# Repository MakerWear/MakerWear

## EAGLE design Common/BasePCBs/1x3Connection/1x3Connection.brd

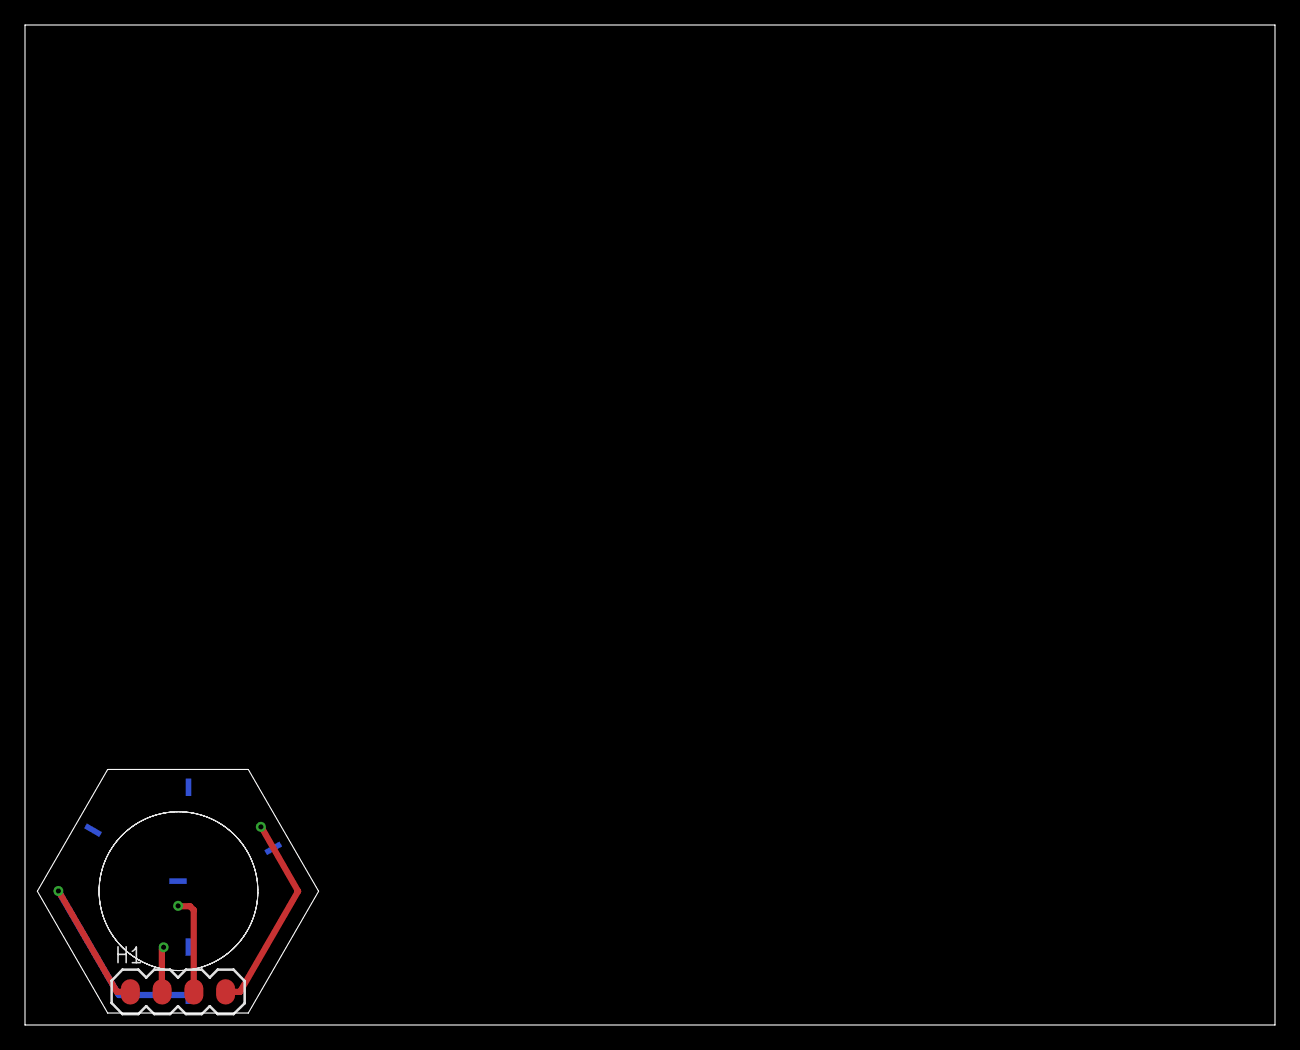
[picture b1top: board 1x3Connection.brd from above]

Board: 2 copper layers, 100.0 x 80.0 mm, 7 parts (0 on the bottom side), 4 nets.

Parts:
CON1, CON2, CON3, CON4, CON5, CON6: SHIELD_FINGER0820; SHIELD_FINGER_PKG
H1: 1X04_NO_HOLES

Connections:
GND: CON4.P1, CON4.P2, H1.3
PWR: CON5.P1, CON5.P2, H1.2
SIN: CON6.P1, CON6.P2, H1.1
SOUT: CON1.P1, CON1.P2, CON2.P1, CON2.P2, CON3.P1, CON3.P2, H1.4

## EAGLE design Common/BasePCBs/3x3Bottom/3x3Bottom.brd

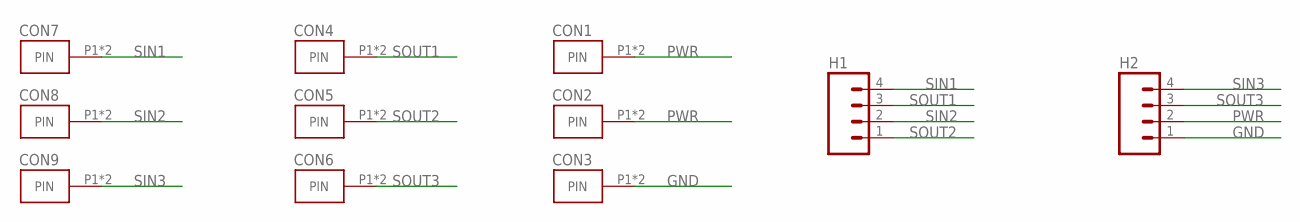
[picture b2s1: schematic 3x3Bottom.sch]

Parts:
CON1, CON2, CON3, CON4, CON5, CON6, CON7, CON8, CON9: SHIELD_FINGER0820; SHIELD_FINGER_PKG
H1, H2: M04; 1X04_NO_HOLES

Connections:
GND: CON3.P1, CON3.P2, H2.1
PWR: CON1.P1, CON1.P2, CON2.P1, CON2.P2, H2.2
SIN1: CON7.P1, CON7.P2, H1.4
SIN2: CON8.P1, CON8.P2, H1.2
SIN3: CON9.P1, CON9.P2, H2.4
SOUT1: CON4.P1, CON4.P2, H1.3
SOUT2: CON5.P1, CON5.P2, H1.1
SOUT3: CON6.P1, CON6.P2, H2.3

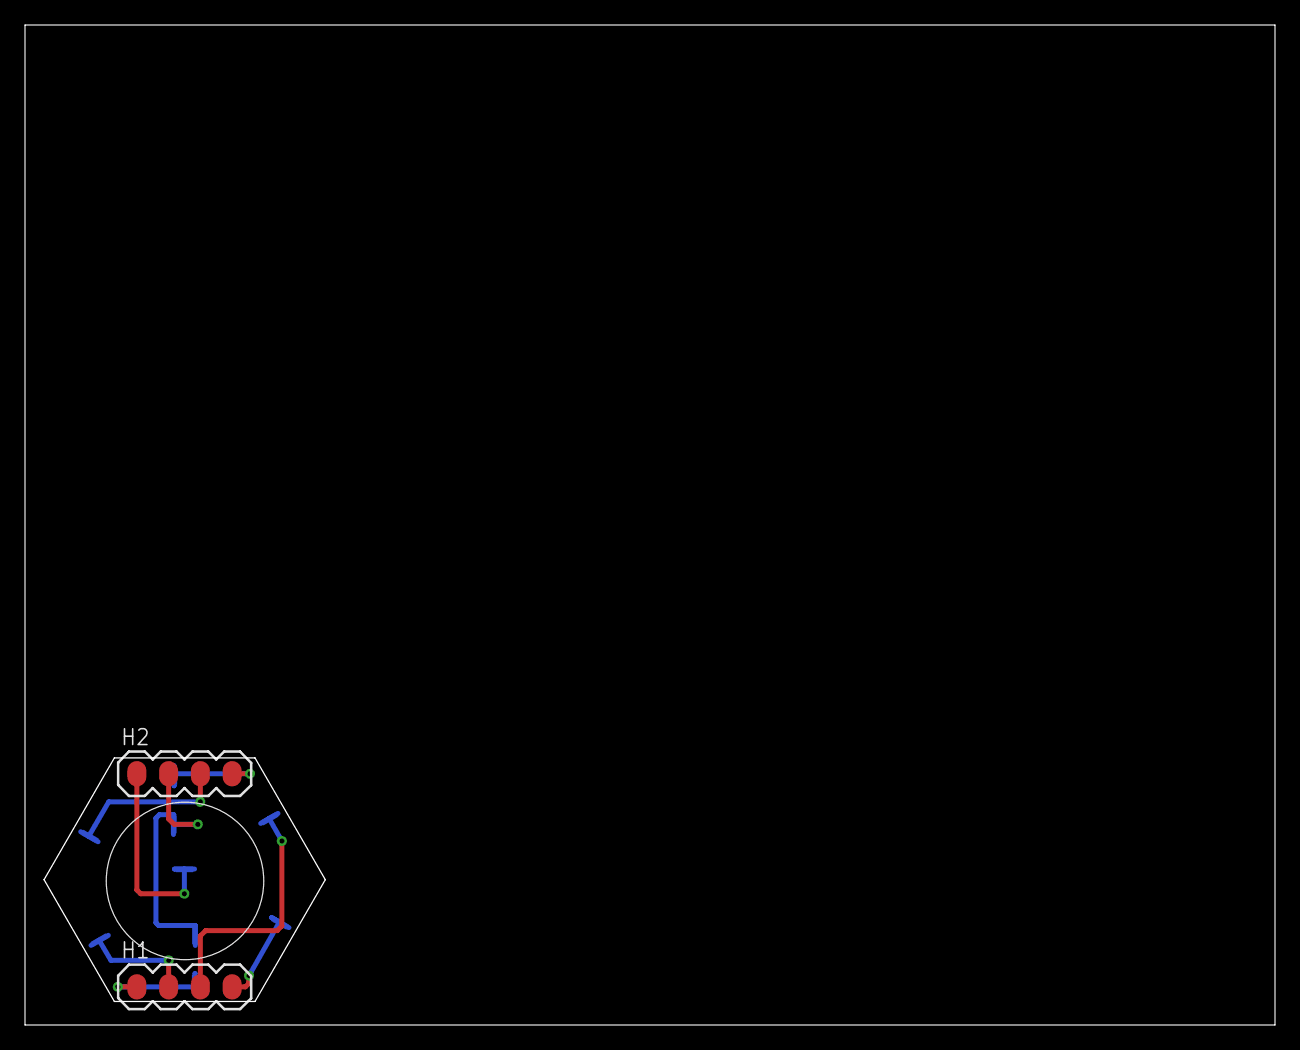
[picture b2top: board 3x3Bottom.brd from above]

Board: 2 copper layers, 100.0 x 80.0 mm, 11 parts (0 on the bottom side), 8 nets.

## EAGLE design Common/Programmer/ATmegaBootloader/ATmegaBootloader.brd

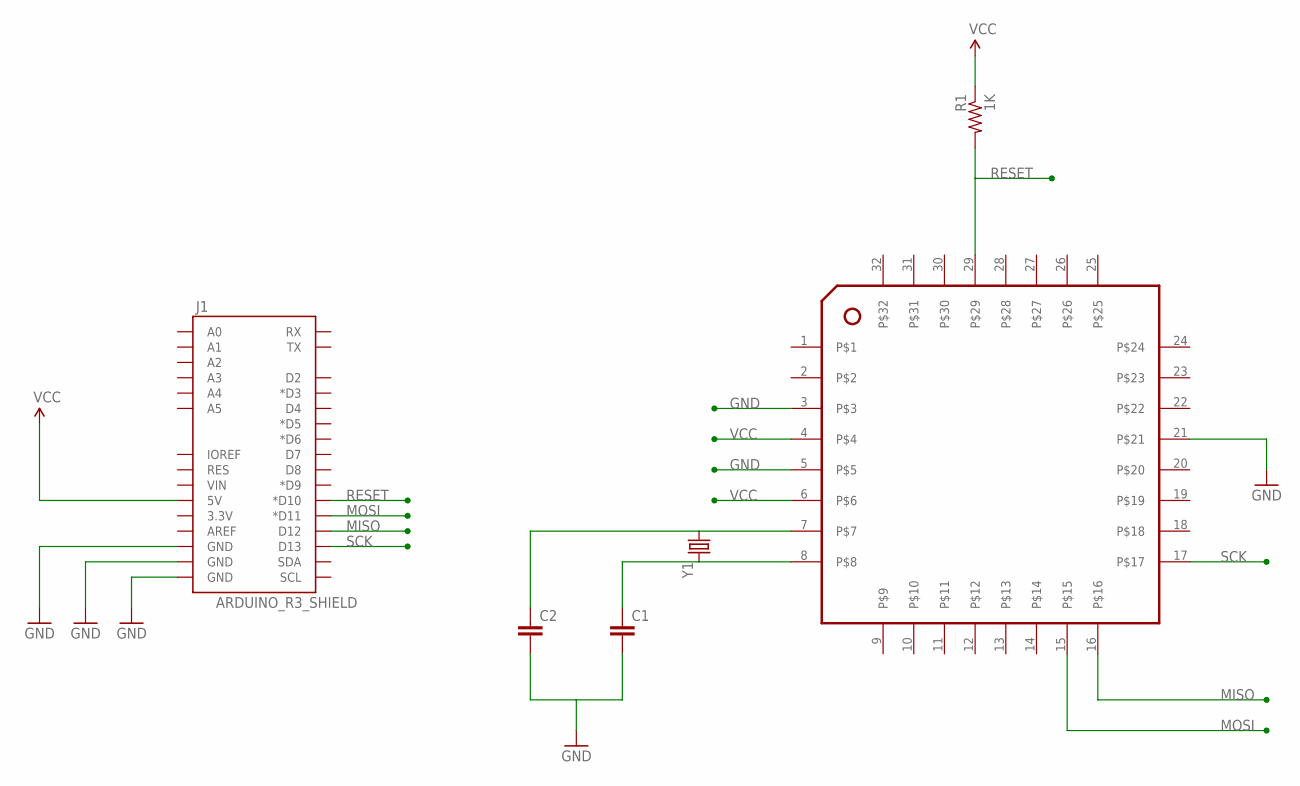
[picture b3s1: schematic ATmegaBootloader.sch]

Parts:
C1, C2: 0.1UF-50V-20%(PTH)KIT-EZ; CAP-PTH-SMALL-KIT
J1: ARDUINO_R3_SHIELD; UNO_R3_SHIELD
R1: 1K; AXIAL-0.3
U$1: ATMEGA-TQFP-BREAKOUT; TQFP32-BREAKOUT
Y1: CRYSTALHC49US; HC49US

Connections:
GND: C1.2, C2.2, J1.GND@0 (GND), J1.GND@1 (GND), J1.GND@2 (GND), U$1.3, U$1.5, U$1.21
MISO: J1.D12, U$1.16
MOSI: J1.D11 (*D11), U$1.15
unnamed: C2.1, U$1.7, Y1.1
unnamed: C1.1, U$1.8, Y1.2
RESET: J1.D10 (*D10), R1.P$2 (2), U$1.29
SCK: J1.D13, U$1.17
VCC: J1.5V, R1.P$1 (1), U$1.4, U$1.6

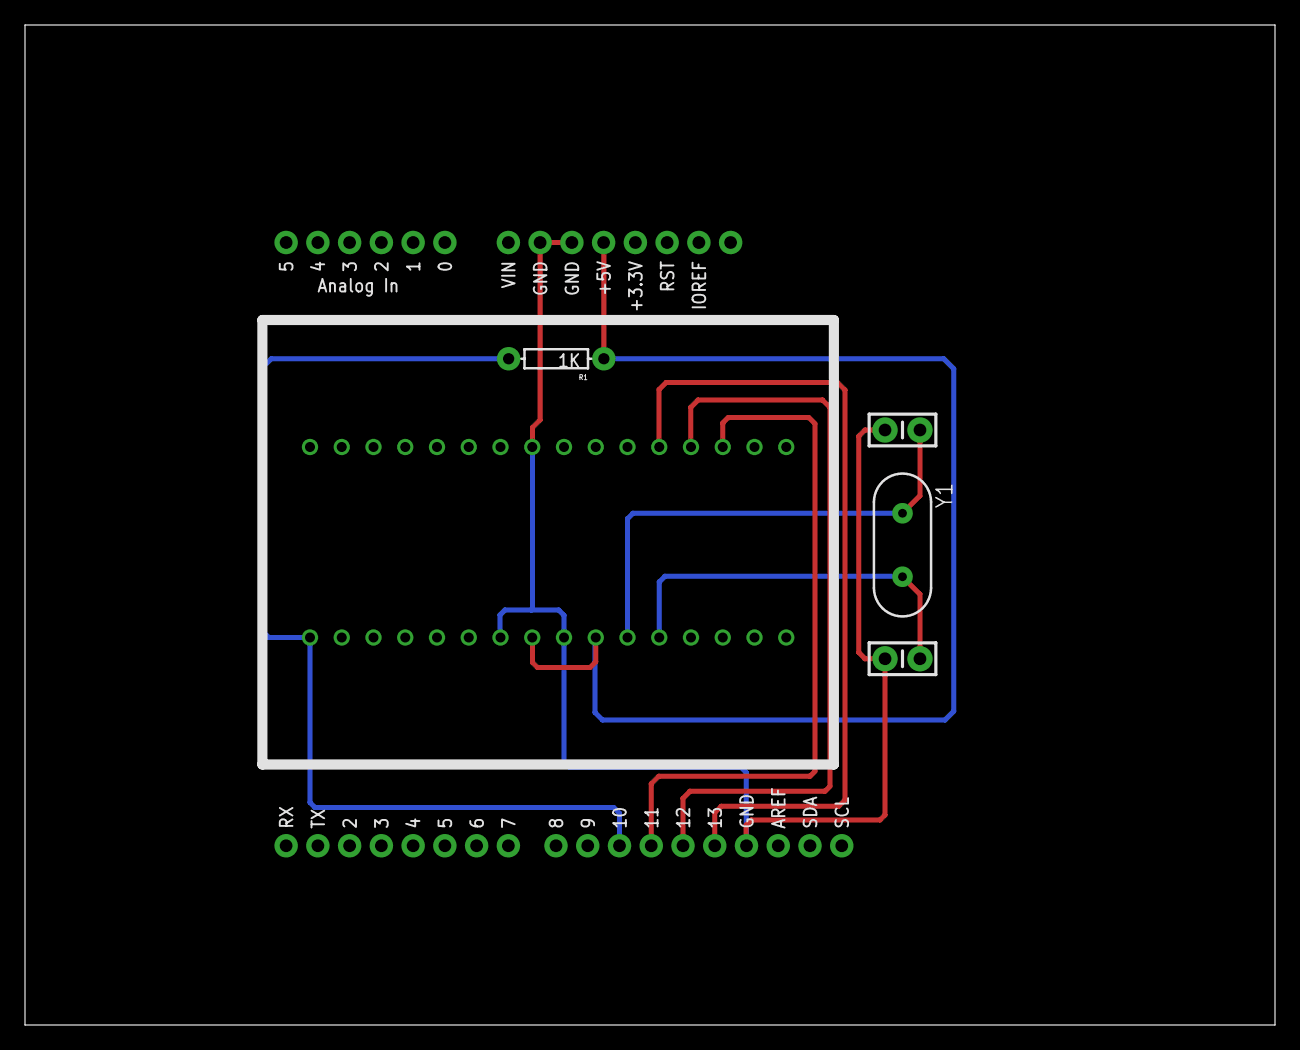
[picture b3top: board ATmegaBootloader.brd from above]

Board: 2 copper layers, 100.0 x 80.0 mm, 6 parts (0 on the bottom side), 8 nets.

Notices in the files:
parts and their libraries:
SparkFun-Connectors: Licensing: Creative Commons ShareAlike 4.0 International - https://creativecommons.org/licenses/by-sa/4.0
